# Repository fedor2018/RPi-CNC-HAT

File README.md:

# RPi CNC HAT

### PCB
- [x] schematic
- [x] fabrication
- [x] soldering
- [x] jtag over network
- [x] external clk

### CPLD
- [x] verilog modules
- [x] quartus compile
- [ ] debug

### Linuxcnc driver
- [x] spi
- [x] rpi clk
- [x] compile
- [ ] debug

### Linuxcnc GUI
- [x] hal
- [x] ini
- [x] schematic
- [ ] pyvcp panel

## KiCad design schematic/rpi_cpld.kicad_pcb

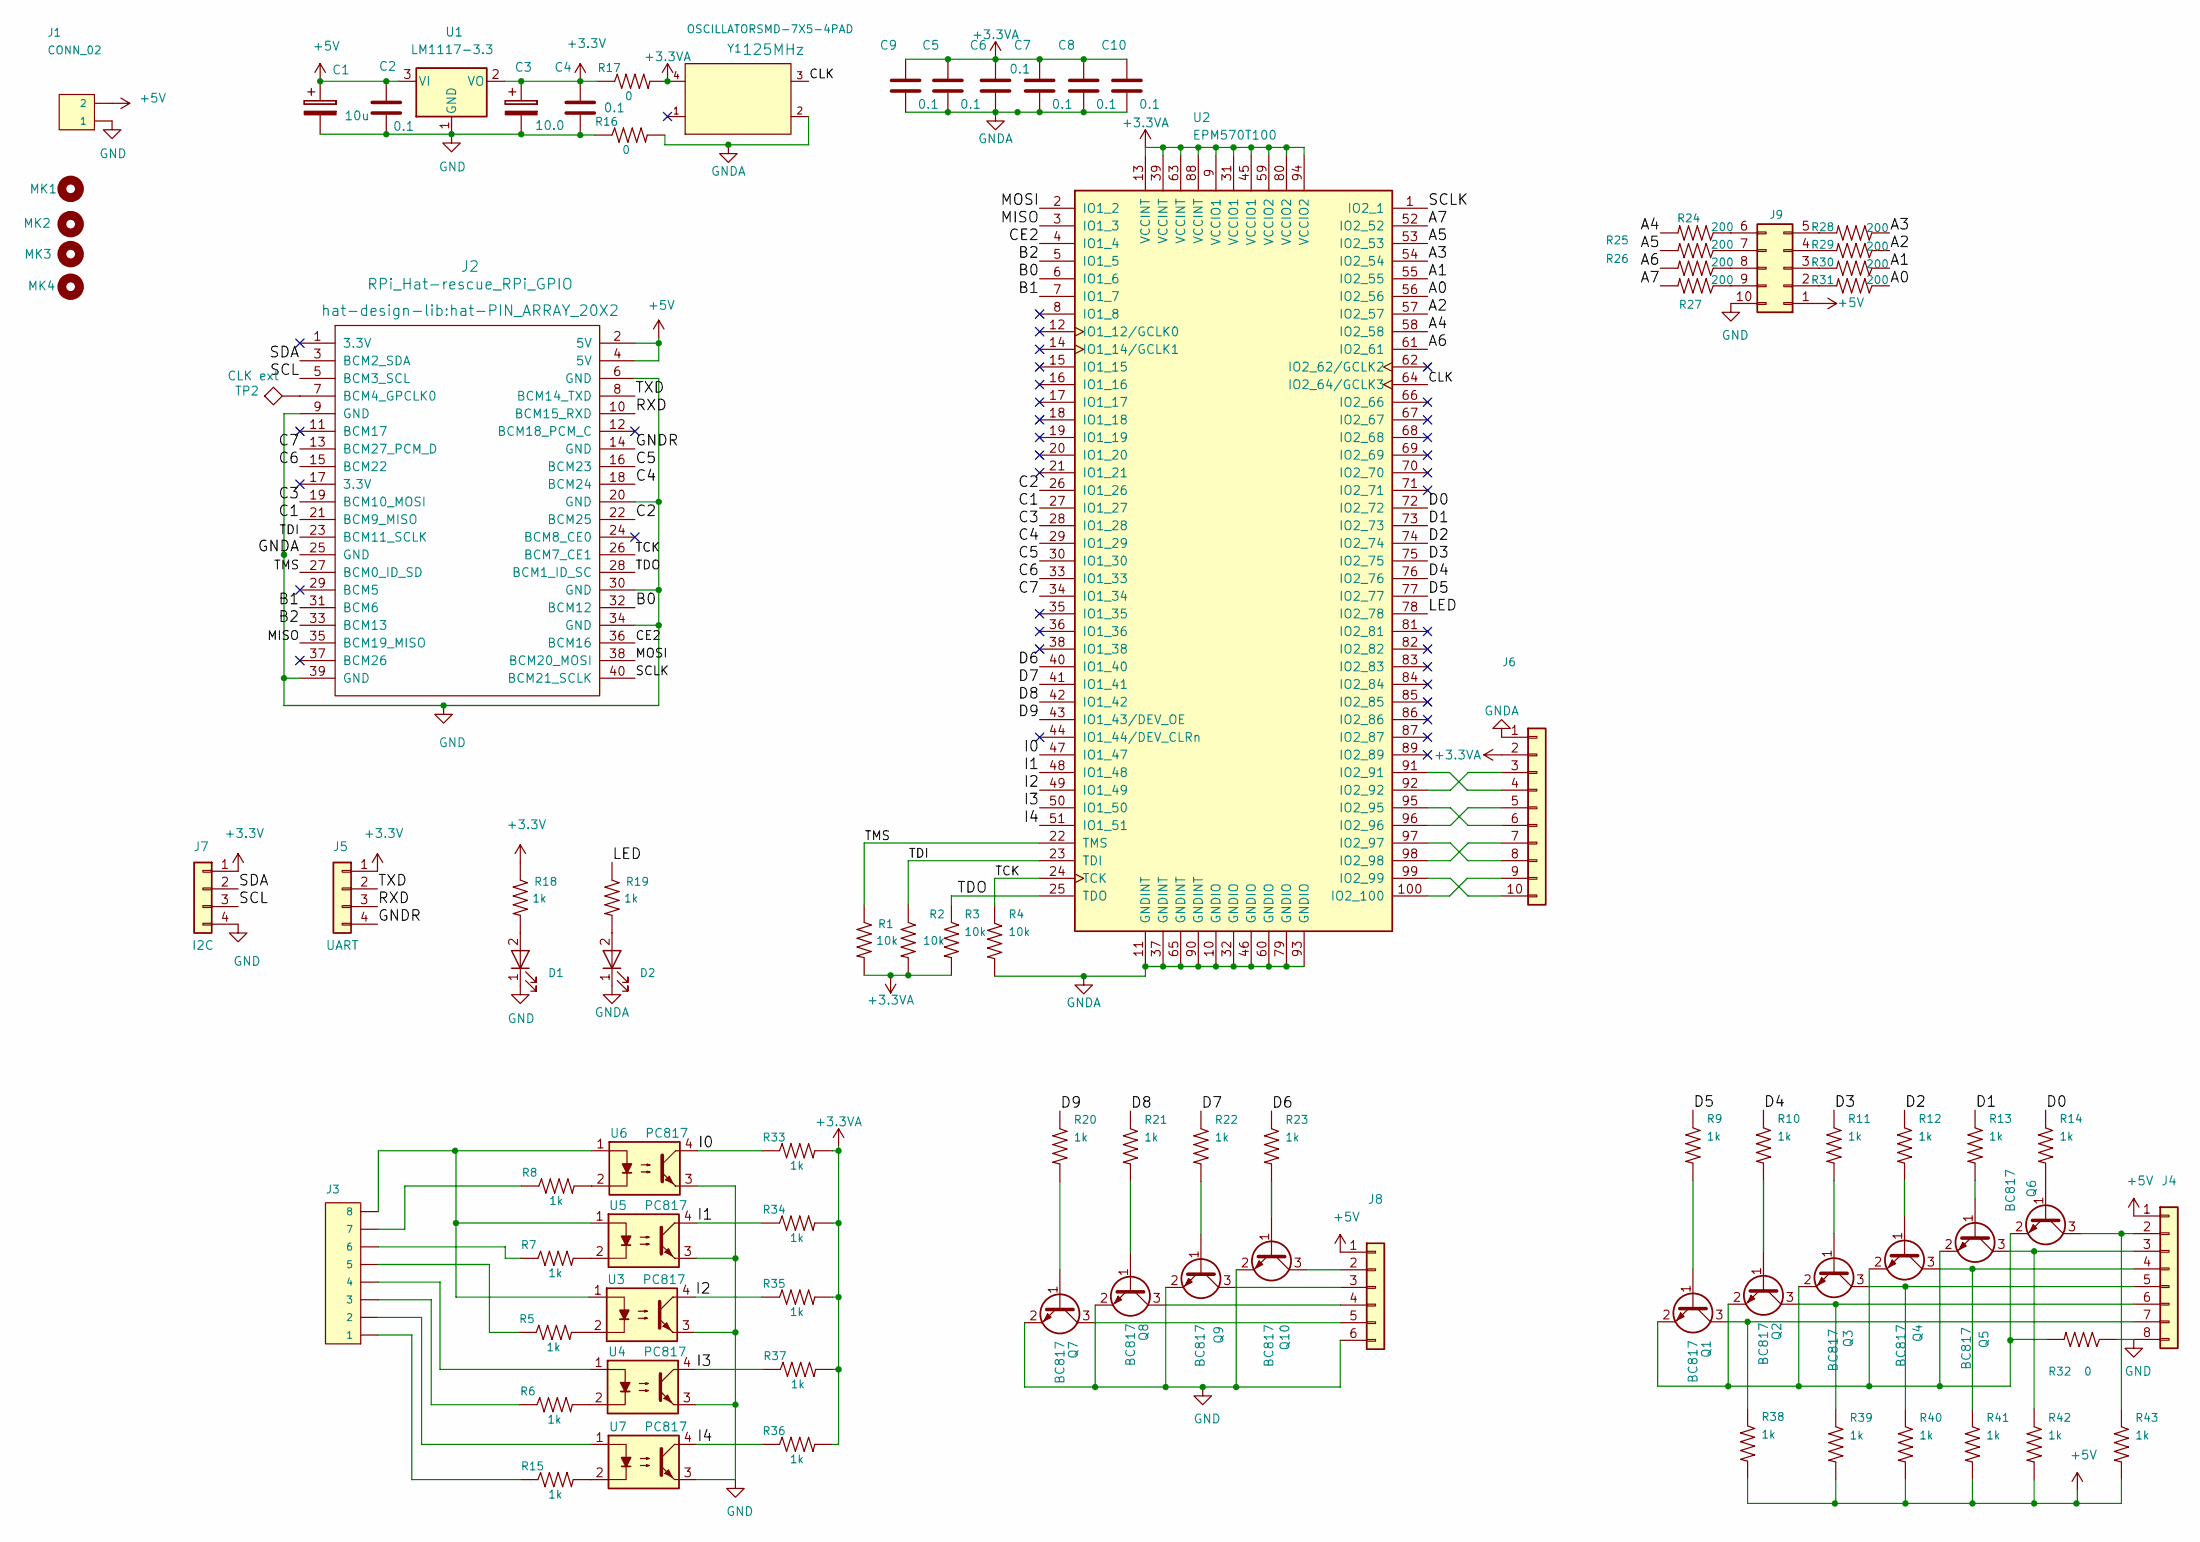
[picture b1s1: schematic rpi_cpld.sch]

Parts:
C1: 10u; C_0805_HandSoldering
C2, C4, C5, C6, C7, C8, C9, C10: 0.1; C_0603_HandSoldering
C3: 10.0; C_0805_HandSoldering
D1, D2: LED-RED0603; LED_0603_HandSoldering
J1: CONN_02; Molex_KK-6410-02_02x2.54mm_Straight
J2: RPi_Hat-rescue_RPi_GPIO; hat-PIN_ARRAY_20X2
J3: JST_EH_B08B-EH-A_08x2.50mm_Straight
J4: Conn_01x10; JST_EH_B08B-EH-A_08x2.50mm_Straight
J5: UART; 1X04
J6, J9: PinHeader_2x05_P2.54mm_Vertical
J7: I2C; 1X04
J8: Conn_01x10; JST_EH_B06B-EH-A_06x2.50mm_Straight
MK1, MK2, MK3, MK4: MountingHole_2.7mm_Pad
Q1, Q2, Q3, Q4, Q5, Q6, Q7, Q8, Q9, Q10: BC817; SOT-23
R1, R2, R3, R4: 10k; C_0603_HandSoldering
R5, R6, R7, R8, R15: 1k; R_0805_HandSoldering
R9, R10, R11, R12, R13, R14, R20, R21, R22, R23, R38, R39, R40, R41, R42, R43: 1k; C_0603_HandSoldering
R16, R17: 0; R_0603_HandSoldering
R18, R19, R33, R34, R35, R36, R37: 1k; R_0603_HandSoldering
R24, R25, R26, R27, R28, R29, R30, R31: 200; C_0603_HandSoldering
R32: 0; C_0603_HandSoldering
TP2: CLK ext; TestPoint_Pad_D1.5mm
U1: LM1117-3.3; SOT-223-3_TabPin2
U2: EPM570T100; LQFP-100_14x14mm_Pitch0.5mm
U3, U4, U5, U6, U7: PC817; DIP-4_W7.62mm
Y1: OSCILLATORSMD-7X5-4PAD; OSCILLATOR-SMD-7X5-4PAD

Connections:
+3.3VA: C5.1, C6.1, C7.1, C8.1, C9.1, C10.1, J6.2, R1.2, R2.2, R3.2, R17.2, R33.2, R34.2, R35.2, R36.2, R37.2, U2.9 (VCCIO1), U2.13 (VCCINT), U2.31 (VCCIO1), U2.39 (VCCINT), U2.45 (VCCIO1), U2.59 (VCCIO2), U2.63 (VCCINT), U2.80 (VCCIO2), U2.88 (VCCINT), U2.94 (VCCIO2), Y1.4 (VCC)
+3V3: C3.1, C4.1, J5.1, J7.1, R17.1, R18.1, U1.2 (VO)
/A0: R31.1, U2.56 (IO2_56)
/A1: R30.1, U2.55 (IO2_55)
/A2: R29.1, U2.57 (IO2_57)
/A3: R28.1, U2.54 (IO2_54)
/A4: R24.2, U2.58 (IO2_58)
/A5: R25.2, U2.53 (IO2_53)
/A6: R26.2, U2.61 (IO2_61)
/A7: R27.2, U2.52 (IO2_52)
/B0: J2.32 (BCM12), U2.6 (IO1_6)
/B1: J2.31 (BCM6), U2.7 (IO1_7)
/B2: J2.33 (BCM13), U2.5 (IO1_5)
/C1: J2.21 (BCM9_MISO), U2.27 (IO1_27)
/C2: J2.22 (BCM25), U2.26 (IO1_26)
/C3: J2.19 (BCM10_MOSI), U2.28 (IO1_28)
/C4: J2.18 (BCM24), U2.29 (IO1_29)
/C5: J2.16 (BCM23), U2.30 (IO1_30)
/C6: J2.15 (BCM22), U2.33 (IO1_33)
/C7: J2.13 (BCM27_PCM_D), U2.34 (IO1_34)
/CE2: J2.36 (BCM16), U2.4 (IO1_4)
/CLK: U2.64 (IO2_64/GCLK3), Y1.3 (OUT)
/D0: R14.1, U2.72 (IO2_72)
/D1: R13.1, U2.73 (IO2_73)
/D2: R12.1, U2.74 (IO2_74)
/D3: R11.1, U2.75 (IO2_75)
/D4: R10.1, U2.76 (IO2_76)
/D5: R9.1, U2.77 (IO2_77)
/D6: R23.1, U2.40 (IO1_40)
/D7: R22.1, U2.41 (IO1_41)
/D8: R21.1, U2.42 (IO1_42)
/D9: R20.1, U2.43 (IO1_43/DEV_OE)
/GNDR: J2.14 (GND), J5.4
/I0: R33.1, U2.47 (IO1_47), U6.4
/I1: R34.1, U2.48 (IO1_48), U5.4
/I2: R35.1, U2.49 (IO1_49), U3.4
/I3: R37.1, U2.50 (IO1_50), U4.4
/I4: R36.1, U2.51 (IO1_51), U7.4
/LED: R19.1, U2.78 (IO2_78)
/MISO: J2.35 (BCM19_MISO), U2.3 (IO1_3)
/MOSI: J2.38 (BCM20_MOSI), U2.2 (IO1_2)
/RXD: J2.10 (BCM15_RXD), J5.3
/SCL: J2.5 (BCM3_SCL), J7.3
/SCLK: J2.40 (BCM21_SCLK), U2.1 (IO2_1)
/SDA: J2.3 (BCM2_SDA), J7.2
/TCK: J2.26 (BCM7_CE1), R4.1, U2.24 (TCK)
/TDI: J2.23 (BCM11_SCLK), R2.1, U2.23 (TDI)
/TDO: J2.28 (BCM1_ID_SC), R3.1, U2.25 (TDO)
/TMS: J2.27 (BCM0_ID_SD), R1.1, U2.22 (TMS)
/TXD: J2.8 (BCM14_TXD), J5.2
GND: C1.2, C2.2, C3.2, C4.2, D1.1 (K), J1.1, J2.6 (GND), J2.9 (GND), J2.20 (GND), J2.30 (GND), J2.34 (GND), J2.39 (GND), J4.8, J7.4, J8.6, J9.10, Q7.2 (E), Q8.2 (E), Q9.2 (E), Q10.2 (E), R16.1, R32.1, U1.1 (GND), U3.3, U4.3, U5.3, U6.3, U7.3
GNDA: C5.2, C6.2, C7.2, C8.2, C9.2, C10.2, D2.1 (K), J2.25 (GND), J6.1, R4.2, R16.2, U2.10 (GNDIO), U2.11 (GNDINT), U2.32 (GNDIO), U2.37 (GNDINT), U2.46 (GNDIO), U2.60 (GNDIO), U2.65 (GNDINT), U2.79 (GNDIO), U2.90 (GNDINT), U2.93 (GNDIO), Y1.2 (GND)
unnamed: D1.2 (A), R18.2
unnamed: D2.2 (A), R19.2
unnamed: J2.7 (BCM4_GPCLK0), TP2.1
unnamed: J3.1, R15.1
unnamed: J3.2, U7.1
unnamed: J3.3, R6.1
unnamed: J3.4, U4.1
unnamed: J3.5, R5.1
unnamed: J3.6, R7.1
unnamed: J3.7, R8.1
unnamed: J3.8, U3.1, U5.1, U6.1
unnamed: J4.2, Q6.3 (C), R43.1
unnamed: J4.3, Q5.3 (C), R42.1
unnamed: J4.4, Q4.3 (C), R41.1
unnamed: J4.5, Q3.3 (C), R40.1
unnamed: J4.6, Q2.3 (C), R39.1
unnamed: J4.7, Q1.3 (C), R38.1
unnamed: J6.3, U2.92 (IO2_92)
unnamed: J6.4, U2.91 (IO2_91)
unnamed: J6.5, U2.96 (IO2_96)
unnamed: J6.6, U2.95 (IO2_95)
unnamed: J6.7, U2.98 (IO2_98)
unnamed: J6.8, U2.97 (IO2_97)
unnamed: J6.9, U2.100 (IO2_100)
unnamed: J6.10, U2.99 (IO2_99)
unnamed: J8.2, Q10.3 (C)
unnamed: J8.3, Q9.3 (C)
unnamed: J8.4, Q8.3 (C)
unnamed: J8.5, Q7.3 (C)
unnamed: J9.2, R31.2
unnamed: J9.3, R30.2
unnamed: J9.4, R29.2
unnamed: J9.5, R28.2
unnamed: J9.6, R24.1
unnamed: J9.7, R25.1
unnamed: J9.8, R26.1
unnamed: J9.9, R27.1
unnamed: Q1.1 (B), R9.2
unnamed: Q1.2 (E), Q2.2 (E), Q3.2 (E), Q4.2 (E), Q5.2 (E), Q6.2 (E), R32.2
unnamed: Q2.1 (B), R10.2
unnamed: Q3.1 (B), R11.2
unnamed: Q4.1 (B), R12.2
unnamed: Q5.1 (B), R13.2
unnamed: Q6.1 (B), R14.2
unnamed: Q7.1 (B), R20.2
unnamed: Q8.1 (B), R21.2
unnamed: Q9.1 (B), R22.2
unnamed: Q10.1 (B), R23.2
unnamed: R5.2, U3.2
unnamed: R6.2, U4.2
unnamed: R7.2, U5.2
unnamed: R8.2, U6.2
unnamed: R15.2, U7.2

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
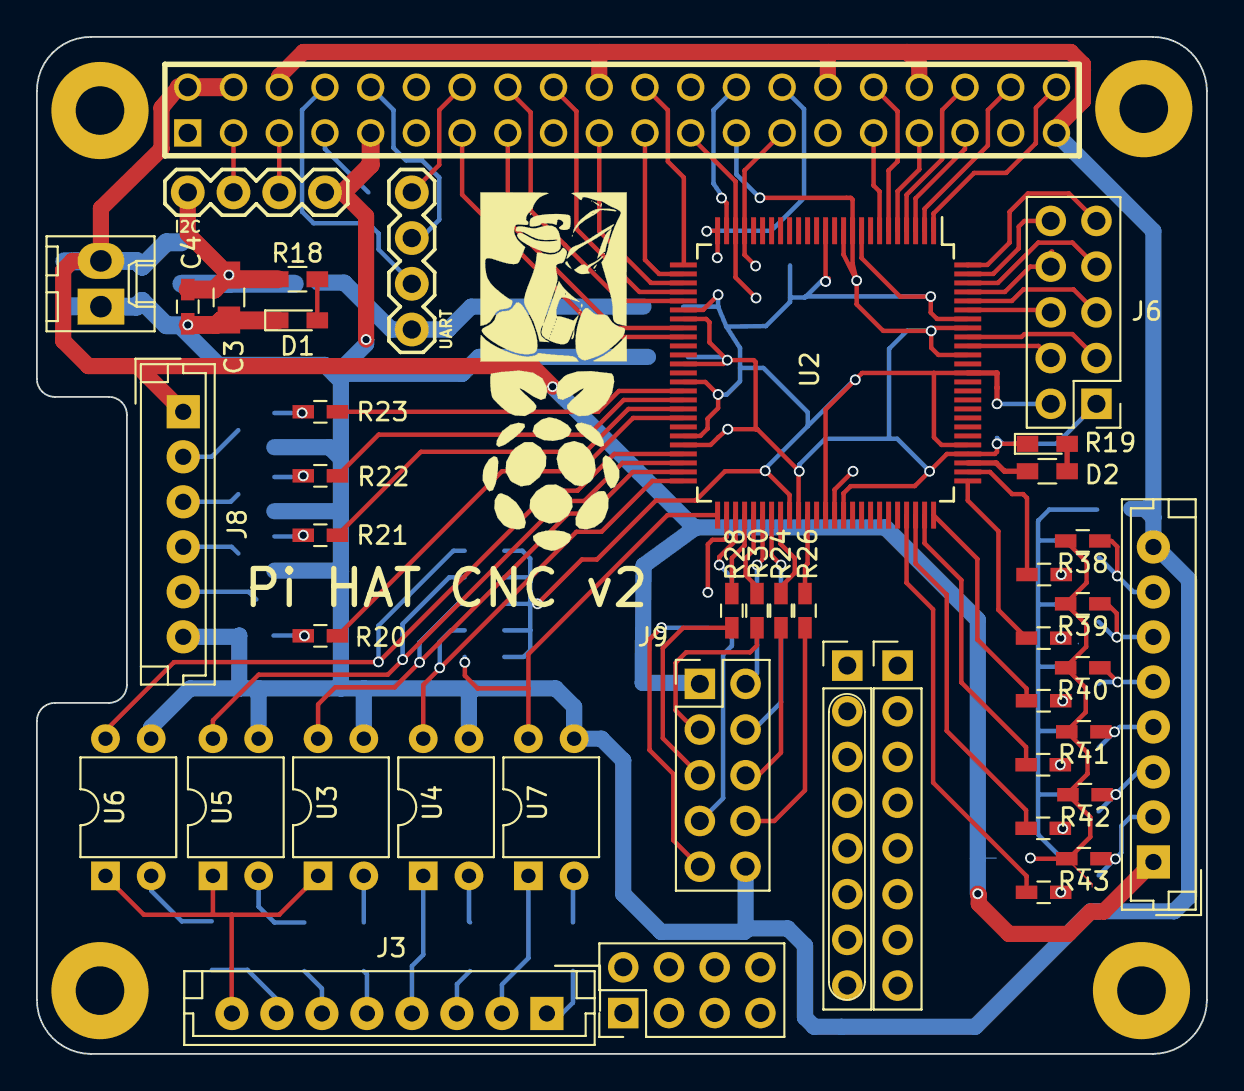
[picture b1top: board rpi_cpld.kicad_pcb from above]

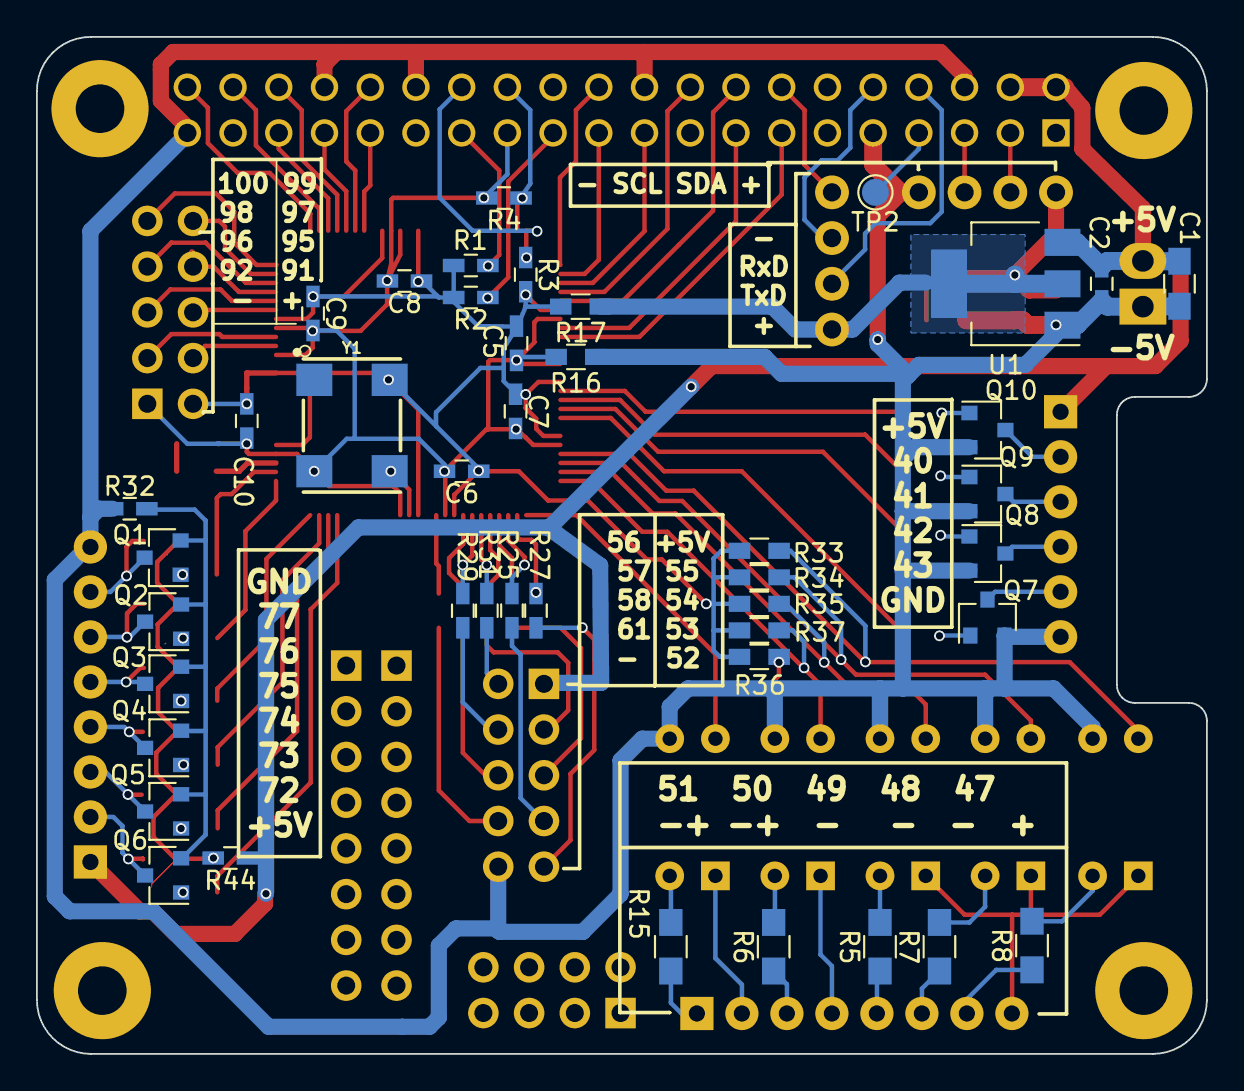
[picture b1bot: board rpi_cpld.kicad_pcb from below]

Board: 2 copper layers, 65.0 x 56.5 mm, 91 parts (43 on the bottom side), 107 nets.

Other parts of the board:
R44: 0; C_0603_HandSoldering
REF00: PinHeader_2x04_P2.54mm_Vertical
REF01, REF02: PinHeader_1x08_P2.54mm_Vertical

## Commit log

2019-01-11 edit
2019-01-11 add first opendrain
2019-01-12 add pwm
2019-01-15 rm file
2019-01-16 add programmer
2019-01-20 info
2019-03-14 update&add
2019-03-30 add dir pin invert
2019-04-02 add kicad5
2019-05-01 add & update
2019-05-05 add tb6600
2019-05-05 fix debug2
2019-09-02 clk=64Mhz
2019-09-02 remove debug2
2019-09-03 port from picnc v2
2019-09-03 debug
2019-09-04 test
2019-09-05 restructuring
2019-09-05 add gpio
2019-09-05 add picnc
2019-09-05 add gpio schematic
2019-09-06 update gpio
2019-09-07 hal gpio
2019-09-07 update gopio schem
2019-09-07 update hal & schema
2019-09-08 gpio hal config
2019-09-11 add hidcomp
2019-09-11 fix compile
2019-09-12 add openxhc
2019-09-13 add config
2019-09-14 add test
2019-09-15 update dir
2019-09-15 rotate screen
2019-09-15 add font
2019-09-15 add st7735 lib
2019-09-16 add fonts
2019-10-25 add files
2019-10-25 new state
